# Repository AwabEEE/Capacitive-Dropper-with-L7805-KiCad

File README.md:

### Capacitive Dropper with L7805<br>
a capacitive dropper AC-to-DC power supply based on the L7805 linear regulator. The design safely steps down mains AC using an X-rated capacitor, rectifier, filtering, and then regulates to a stable 5V DC.

### Repository Contents :
kicad_sch – KiCad schematic<br>
kicad_pcb – KiCad PCB layout
<br>
<br>

### 🛠️ Tools Used
KiCad (v9.03)

🖼️ Previews
### **Schematic** :

<br>
### Circuit Explanation
This circuit is a capacitive dropper type power supply:<br>
AC Input → Connected to mains (high voltage, dangerous).<br>
X-rated Capacitor + Resistor → Limits AC current without dissipating much heat (capacitive reactance acts as a "resistor"). The series resistor also helps limit inrush current and improves safety.
<br>
Rectifier → Diodes convert AC to pulsating DC.<br>
Smoothing Capacitor → Provides a DC rail with ripple removed.<br>
L7805 Regulator → Provides a stable +5V output for low-power electronics.<br>
Bypass Capacitors → On regulator input and output for stability.<br>
Load Output → Clean, regulated +5V DC.<br>
<br>
<br>
###  Important Note: A capacitive dropper has no galvanic isolation from mains. It should only be used for low-power embedded circuits in fully enclosed designs where safety is guaranteed.
<br>
<br>

### **PCB** :

<br>
<br>

## 📜 License
This project is licensed under [CC0 1.0](https://creativecommons.org/publicdomain/zero/1.0/),  
which dedicates it to the public domain.

### ✨ Author
Awab– @AwabEEE

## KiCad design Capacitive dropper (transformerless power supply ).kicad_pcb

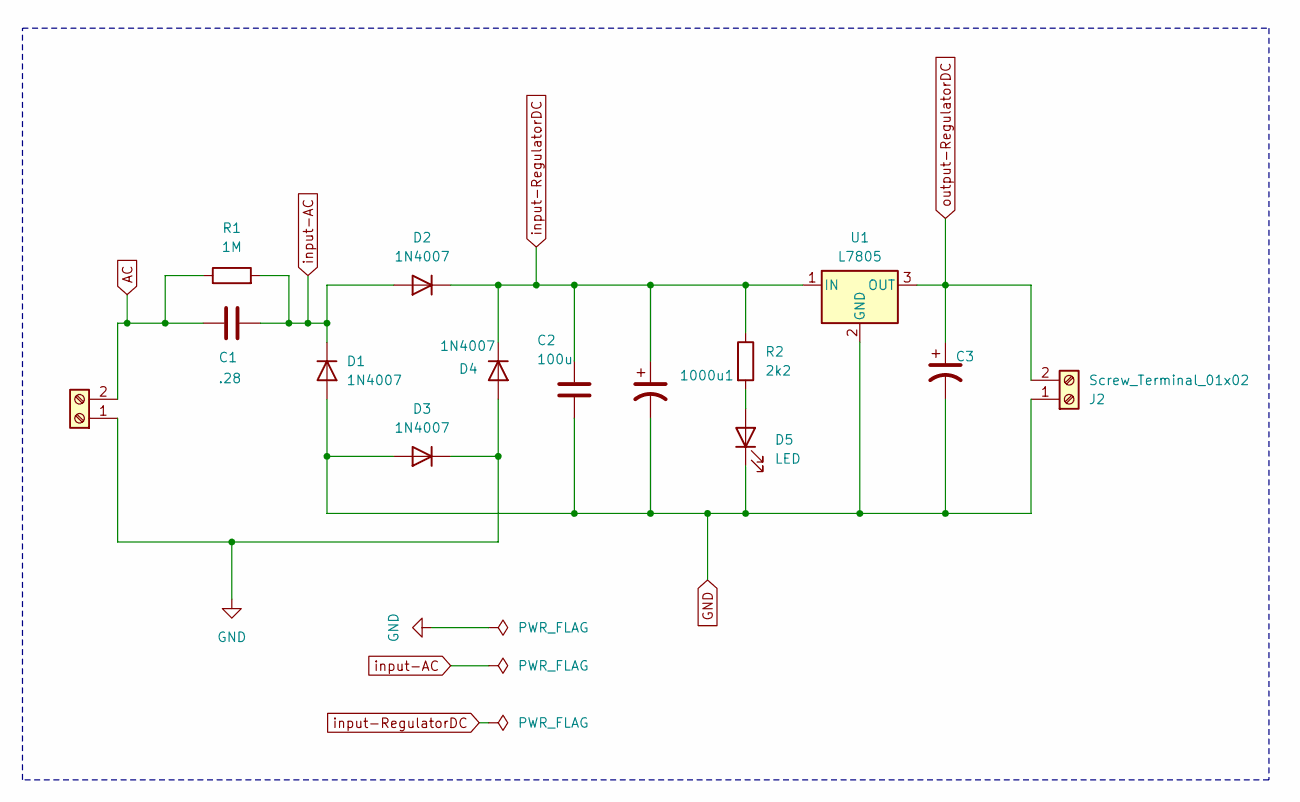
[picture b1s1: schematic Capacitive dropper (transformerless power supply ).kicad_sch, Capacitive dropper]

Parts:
1000u1: C_Polarized_US; CP_Radial_D8.0mm_P3.50mm
C1: .28; C_Disc_D4.3mm_W1.9mm_P5.00mm
C2: 100u; CP_Radial_D8.0mm_P3.50mm
C3: 1000u; CP_Radial_D8.0mm_P3.50mm
D1, D2, D3, D4: 1N4007; D_DO-41_SOD81_P10.16mm_Horizontal
D5: LED; LED_D8.0mm
J1, J2: Screw_Terminal_01x02; TerminalBlock_bornier-2_P5.08mm
R1: 1M; R_Axial_DIN0207_L6.3mm_D2.5mm_P7.62mm_Horizontal
R2: 2k2; R_Axial_DIN0207_L6.3mm_D2.5mm_P7.62mm_Horizontal
U1: L7805; TO-220-3_Vertical

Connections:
AC: C1.2, J1.2, R1.1
GND: 1000u1.2, C2.2, C3.2, D1.2 (A), D3.1 (K), D3.2 (A), D4.2 (A), D5.1 (K), J1.1, J2.1, U1.2 (GND)
unnamed: D5.2 (A), R2.2
input-AC: C1.1, D1.1 (K), D2.2 (A), R1.2
input-RegulatorDC: 1000u1.1, C2.1, D2.1 (K), D4.1 (K), R2.1, U1.1 (IN)
output-RegulatorDC: C3.1, J2.2, U1.3 (OUT)

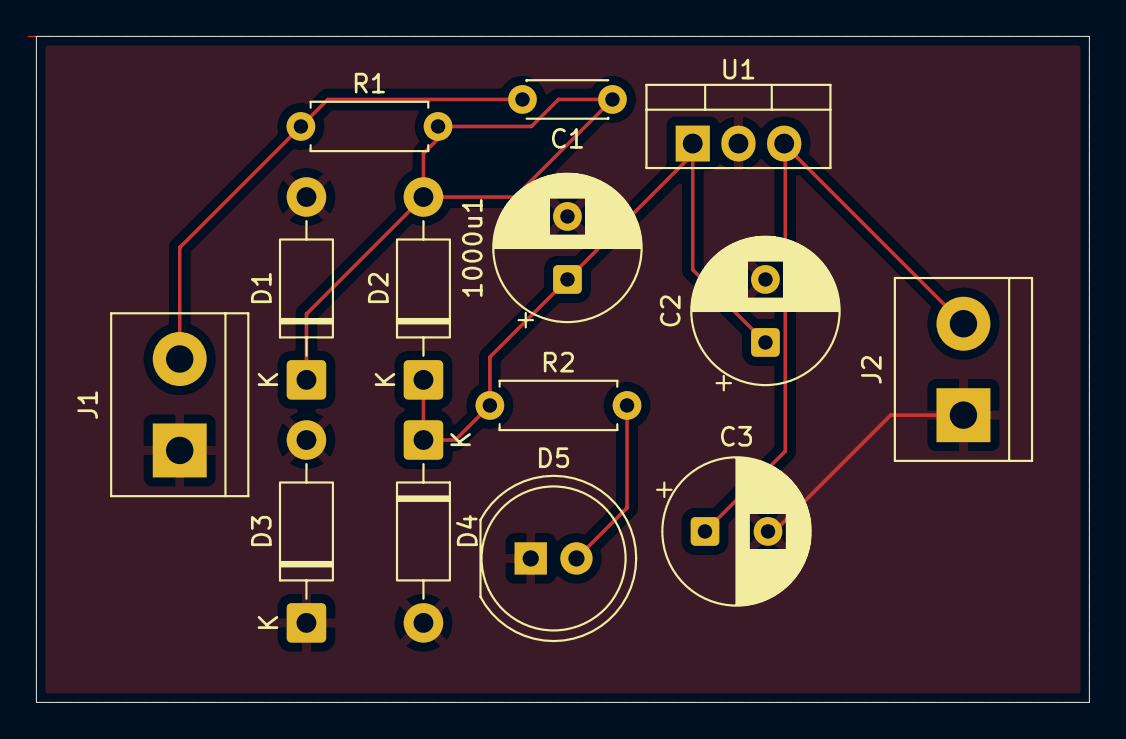
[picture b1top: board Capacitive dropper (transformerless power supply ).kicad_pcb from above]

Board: 2 copper layers, 58.5 x 37.0 mm, 14 parts (0 on the bottom side), 6 nets.

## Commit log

2025-08-17 Schematic and PCB
2025-08-17 Screenshots
2025-08-17 Rename Screenshot 2025-08-17 031116.png to schematic.png
2025-08-17 rename
2025-08-17 Rename Capacitive dropper (transformerless power supply )3.png to view2.png
2025-08-17 Rename Capacitive dropper (transformerless power supply )4.png to view4.png
2025-08-17 Rename schematic.png to PCBscreenshot.png
2025-08-17 Rename Screenshot 2025-08-17 032500.png to SchematicScreenshot.png
2025-08-17 README.md
